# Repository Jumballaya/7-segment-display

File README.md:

# 7 Segment Display Component

This is the code repository for the 7 Segment Display Component I created. In the code folder there is the example code used in the post detailing how to prototype, design and build a custom component.

The component is made up of an 8-bit shift register (74HC595) and a 7 segment display. It was chosen because I wanted a simple project to explore designing a custom PCB and having it printed.

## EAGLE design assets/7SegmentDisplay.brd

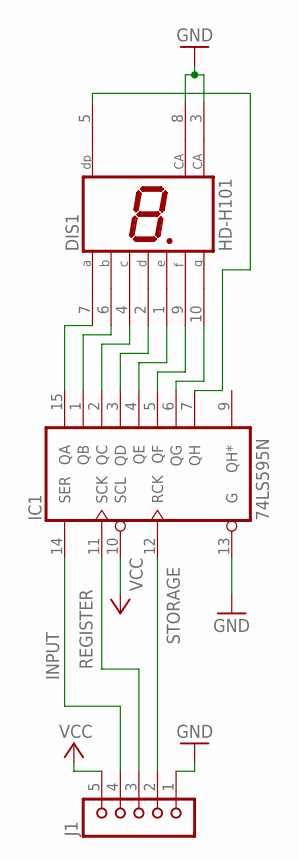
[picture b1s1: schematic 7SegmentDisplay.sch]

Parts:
DIS1: HD-H101; HDSP-M
IC1: 74LS595N; DIL16
J1: JU05

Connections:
GND: DIS1.3 (CA), DIS1.8 (CA), IC1.8 (GND), IC1.13 (G), J1.1
INPUT: IC1.14 (SER), J1.4
unnamed: DIS1.7 (A), IC1.15 (QA)
unnamed: DIS1.6 (B), IC1.1 (QB)
unnamed: DIS1.4 (C), IC1.2 (QC)
unnamed: DIS1.2 (D), IC1.3 (QD)
unnamed: DIS1.1 (E), IC1.4 (QE)
unnamed: DIS1.9 (F), IC1.5 (QF)
unnamed: DIS1.10 (G), IC1.6 (QG)
unnamed: DIS1.5 (DP), IC1.7 (QH)
REGISTER: IC1.11 (SCK), J1.3
STORAGE: IC1.12 (RCK), J1.2
VCC: IC1.10 (SCL), IC1.16 (VCC), J1.5

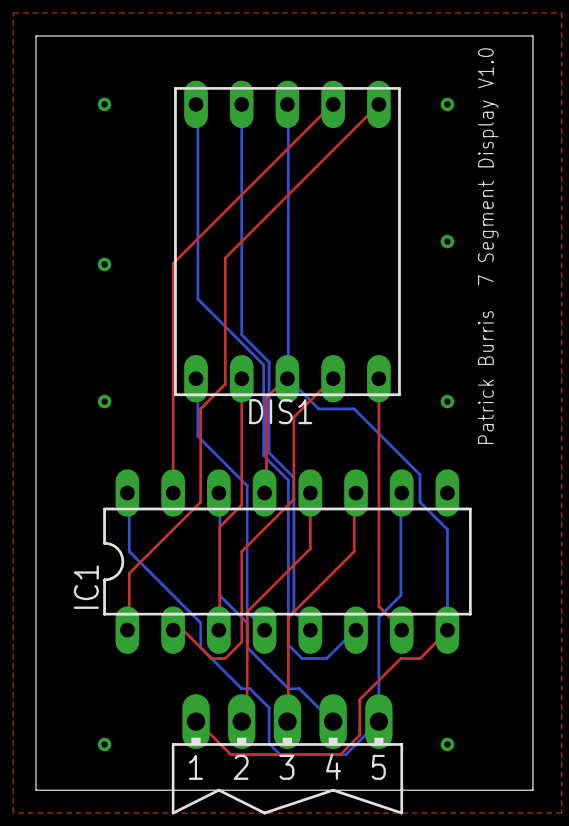
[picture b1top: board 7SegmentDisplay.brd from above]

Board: 2 copper layers, 27.6 x 41.9 mm, 3 parts (0 on the bottom side), 13 nets.

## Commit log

2019-07-26 add example code for testing
2019-07-26 add basic readme
2019-07-28 add example with 2 components
2019-07-28 add eagle cad assets
